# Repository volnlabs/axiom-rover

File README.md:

# Axiom Rover

**Interactive 3D inspection:** [open the hosted viewer](https://axiom-rover.vercel.app/) or [inspect the PCB](https://axiom-rover.vercel.app/?mode=pcb) — rotate, zoom, inspect all sides, hide the shell, or separate parts. [Local viewing and deployment instructions](viewer/README.md).

After cloning, use [the Git LFS checkout instructions](docs/build.md) to download the full assembly STEP, Pi reference STEP and viewer mesh before opening or rebuilding them.

A reusable 2WD release-test robot: one fixed Shrike/RP2040 + ForgeFPGA actuator base, a removable compute tray, an independent motor-power stop, and a wheels-raised stand. This is an **independent hardware repository**, not part of the AxiomOS source tree.

**Revision B is a design-review prototype, not released for fabrication or powered motion.** The carrier now has a bottom Pi 5 socket, two top Shrike R0.4 sockets, an onboard DRV8833 motor driver, and HC-SR04, wheel-encoder and IMU connectors. Vendor CAD and nominal socket models establish design coordinates; physical fit and powered tests remain outstanding.

- [Editable KiCad project](electronics/carrier.kicad_pro), [schematic](electronics/carrier.kicad_sch), [routed PCB](electronics/carrier.kicad_pcb), and [schematic drawing](electronics/out/schematic/carrier.svg).
- [Parametric mechanical source](mechanical/axiom_rover.py), [STEP assembly](mechanical/out/axiom_rover_assembly.step), and individual STL parts in [mechanical/out](mechanical/out/).
- [Electrical and harness contract](docs/electrical-contract.md), [wiring diagram](docs/harness.svg), [mechanical interfaces](docs/mechanical.md), [system BOM](bom/system-bom.csv).
- [Assembly, procurement and commissioning](docs/commissioning.md), [post-v1.0 compute roadmap](docs/compute-roadmap.md), [reproduction instructions](docs/build.md).
- [Controller bench fixture and motor-disconnected test procedure](docs/bench.md).
- [Native electrical check results](electronics/out/drc.json), [mechanical checks](mechanical/out/mechanical_checks.json), [populated assembly checks](mechanical/out/assembly-fit.json), [42 browser checks](viewer/browser-check.json), and [release gates](release-gates.json).

The carrier is 160 × 100 × 1.6 mm, two layers, with a cooler aperture. The Pi sits below it at a 16.5 mm gap and Shrike plugs into two 19-position sockets above. Two 6 V ThinkRobotics MOT3001-6V60RPM encoder motors drive 80 mm Pololu 3690 wheels. DRV8833 current regulation targets 1 A per channel; actual current and thermal behavior require bench measurements. The external fuse, normally-open motor-power relay, regulated motor source and separate host/base supplies remain off-board. Power down before compute swaps; J1 and alternate-host J12 cannot be used together.

A robot supplies repeatable evidence for named releases and fault cases. It cannot prove AxiomOS correct under every possible condition. Every physical result must identify the software/FPGA hashes, hardware revision, power state and raw capture.

Budget cap: ₹30,000 excluding compute boards and instruments, with ₹6,000 reserved for a revision. The current estimate is ₹20,821.98–₹45,459.98 before reserve (₹26,821.98–₹51,459.98 including it), not a vendor quote. First-order quotes must total at most ₹24,000 before ordering. Nothing has been purchased, fabricated, flashed or physically tested here.

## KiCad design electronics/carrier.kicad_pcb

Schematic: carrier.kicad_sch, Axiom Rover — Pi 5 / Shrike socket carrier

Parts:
C1, C2, C3, C4, C9: 100nF 16V X7R; C_0805_2012Metric
C5: 10uF 16V X7R; C_1206_3216Metric
C6: 10nF 25V X7R; C_0805_2012Metric
C7: 2.2uF 16V X7R; C_0805_2012Metric
C8: 470uF 16V; CP_Radial_D8.0mm_P3.50mm
D1: SMBJ6.0A; D_SMB
J1: ESQ-120-24-G-D_PI5_BOTTOM; Pi5_Socket_2x20
J2: SHRIKE_J2_SSW-119-01-G-S; SSW-119-01-G-S
J3: HC_SR04_VCC_TRIG_ECHO_GND; JST_XH_B4B-XH-A_1x04_P2.50mm_Vertical
J4: SHRIKE_J4_SSW-119-01-G-S; SSW-119-01-G-S
J5: ESTOP_LOGIC_NC; JST_XH_B2B-XH-A_1x02_P2.50mm_Vertical
J6: BASE_SENSOR_5V_IN; JST_XH_B2B-XH-A_1x02_P2.50mm_Vertical
J7: 6V_AFTER_FUSE_AND_STOP_RELAY; JST_VH_B2P-VH_1x02_P3.96mm_Vertical
J8: LEFT_MOTOR; JST_VH_B2P-VH_1x02_P3.96mm_Vertical
J9: RIGHT_MOTOR; JST_VH_B2P-VH_1x02_P3.96mm_Vertical
J10: ENCODER_LEFT_3V3; JST_XH_B4B-XH-A_1x04_P2.50mm_Vertical
J11: ENCODER_RIGHT_3V3; JST_XH_B4B-XH-A_1x04_P2.50mm_Vertical
J12: ALTERNATE_HOST_UART; JST_XH_B4B-XH-A_1x04_P2.50mm_Vertical
J13: IMU_3V3_I2C_INT; JST_XH_B5B-XH-A_1x05_P2.50mm_Vertical
R1, R16, R17, R18, R19: 1k 1%; R_0805_2012Metric
R2: 2.2k 1%; R_0805_2012Metric
R3: 3.3k 1%; R_0805_2012Metric
R4, R5, R6, R9, R10, R11, R12, R13: 10k 1%; R_0805_2012Metric
R7, R8: 0.20R 1W CSRT1206FTR200; R_1206_3216Metric
R14, R15: 4.7k 1%; R_0805_2012Metric
TP1: HOST_3V3; TestPoint_Pad_D1.5mm
TP2: H_GND; TestPoint_Pad_D1.5mm
TP3: BASE_3V3; TestPoint_Pad_D1.5mm
TP4: BASE_5V; TestPoint_Pad_D1.5mm
TP5: MOTOR_6V; TestPoint_Pad_D1.5mm
TP6: BASE_GND; TestPoint_Pad_D1.5mm
TP7: ESTOP_N; TestPoint_Pad_D1.5mm
TP8: DRV_FAULT_N; TestPoint_Pad_D1.5mm
TP9: SENSE_L; TestPoint_Pad_D1.5mm
TP10: SENSE_R; TestPoint_Pad_D1.5mm
U1: ISO7721DR; SOIC-8_3.9x4.9mm_P1.27mm
U2: SN74LVC1G17DBVR; SOT-23-5
U3: DRV8833PWPR; HTSSOP-16-1EP_4.4x5mm_P0.65mm_EP3.4x5mm_Mask2.46x2.31mm_The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
U4: SN74LVC08ADR; SOIC-14_3.9x8.7mm_P1.27mm
U5: SN74LVC125ADR; SOIC-14_3.9x8.7mm_P1.27mm

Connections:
/BASE_3V3: C2.1, C3.1, C4.1, C9.1, J2.2, J4.2, J5.1, J10.2, J11.2, J13.2, R9.2, R14.2, R15.2, TP3.1, U1.8 (VCC2), U2.5 (VCC), U4.14 (VCC), U5.14 (VCC)
/BASE_5V: J3.1, J6.1, TP4.1
/BASE_GND: C2.2, C3.2, C4.2, C5.2, C7.2, C8.2, C9.2, D1.2 (A), J2.8, J2.13, J3.4, J4.7, J4.13, J4.19, J6.2, J7.2, J10.1, J11.1, J13.1, R3.2, R4.2, R5.2, R6.2, R7.2, R8.2, R10.2, R11.2, R12.2, R13.2, TP6.1, U1.5 (GND2), U2.3 (GND), U3.13 (GND), U3.17 (EP), U4.7 (GND), U5.1 (1OE_N), U5.4 (2OE_N), U5.7 (GND), U5.10 (3OE_N), U5.13 (4OE_N)
/DRV_AIN1: U3.16 (AIN1), U4.3 (1Y)
/DRV_AIN2: U3.15 (AIN2), U4.6 (2Y)
/DRV_BIN1: U3.9 (BIN1), U4.8 (3Y)
/DRV_BIN2: U3.10 (BIN2), U4.11 (4Y)
/DRV_FAULT_N: R9.1, TP8.1, U3.8 (nFAULT), U5.9 (3A), U5.12 (4A)
/DRV_VCP: C6.1, U3.11 (VCP)
/DRV_VINT: C7.1, U3.14 (VINT)
/ECHO_DIV: R2.2, R3.1, U2.2 (A)
/ENC_L_A: J4.14, J10.3
/ENC_L_B: J4.12, J10.4
/ENC_R_A: J4.11, J11.3
/ENC_R_B: J4.10, J11.4
/ESTOP_FPGA: J2.16, R17.2
/ESTOP_FPGA_DRIVE: R17.1, U5.6 (2Y)
/ESTOP_N: J5.2, R4.1, TP7.1, U3.1 (nSLEEP), U5.2 (1A), U5.5 (2A)
/ESTOP_RP: J2.3, R16.2
/ESTOP_RP_DRIVE: R16.1, U5.3 (1Y)
/FAULT_FPGA_DRIVE: R19.1, U5.11 (4Y)
/FAULT_FPGA_N: J2.19, R19.2
/FAULT_RP_DRIVE: R18.1, U5.8 (3Y)
/FAULT_RP_N: J4.4, R18.2
/FPGA_PWM_L: J2.17, R5.1, U4.2 (1B), U4.5 (2B)
/FPGA_PWM_R: J2.18, R6.1, U4.10 (3B), U4.13 (4B)
/HOST_3V3: C1.1, J1.1, J1.17, J12.1, TP1.1, U1.1 (VCC1)
/H_GND: C1.2, J1.6, J1.9, J1.14, J1.20, J1.25, J1.30, J1.34, J1.39, J12.2, TP2.1, U1.4 (GND1)
/H_RX: J1.10, J12.4, U1.2 (OUTA)
/H_TX: J1.8, J12.3, U1.3 (INB)
/IMU_INT: J4.3, J13.5
/IMU_SCL: J4.5, J13.4, R15.1
/IMU_SDA: J4.6, J13.3, R14.1
/L_IN1: J2.4, R10.1, U4.1 (1A)
/L_IN2: J2.5, R11.1, U4.4 (2A)
/MOTOR_6V: C5.1, C6.2, C8.1, D1.1 (K), J7.1, TP5.1, U3.12 (VM)
/MOTOR_L_N: J8.2, U3.4 (AOUT2)
/MOTOR_L_P: J8.1, U3.2 (AOUT1)
/MOTOR_R_N: J9.2, U3.5 (BOUT2)
/MOTOR_R_P: J9.1, U3.7 (BOUT1)
/RP_UART_RX: J4.17, U1.6 (OUTB)
/RP_UART_TX: J4.18, U1.7 (INA)
/R_IN3: J2.6, R12.1, U4.9 (3A)
/R_IN4: J2.7, R13.1, U4.12 (4A)
/SENSE_L: R7.1, TP9.1, U3.3 (AISEN)
/SENSE_R: R8.1, TP10.1, U3.6 (BISEN)
/SENSOR_TRIG: J3.2, R1.2
/US_ECHO_3V: J2.10, U2.4 (Y)
/US_ECHO_5V: J3.3, R2.1
/US_TRIG: J2.9, R1.1

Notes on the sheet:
REV B.1: Pi 5 bottom socket + Shrike R0.4 top sockets; no host/base ground tie
J7: REGULATED 6 V AFTER EXTERNAL FUSE + INDEPENDENT STOP RELAY. 1 A nominal per motor.
FPGA PWM gates direction inputs through U4. nSLEEP is STOP level, never PWM.
Shrike USB-C is sole 5 V power entry. J1 pins 2/4 and J2/J4 pin 1 stay disconnected.
REVIEW ONLY: physical fit, current limit, cooling and firmware timing require bench evidence.

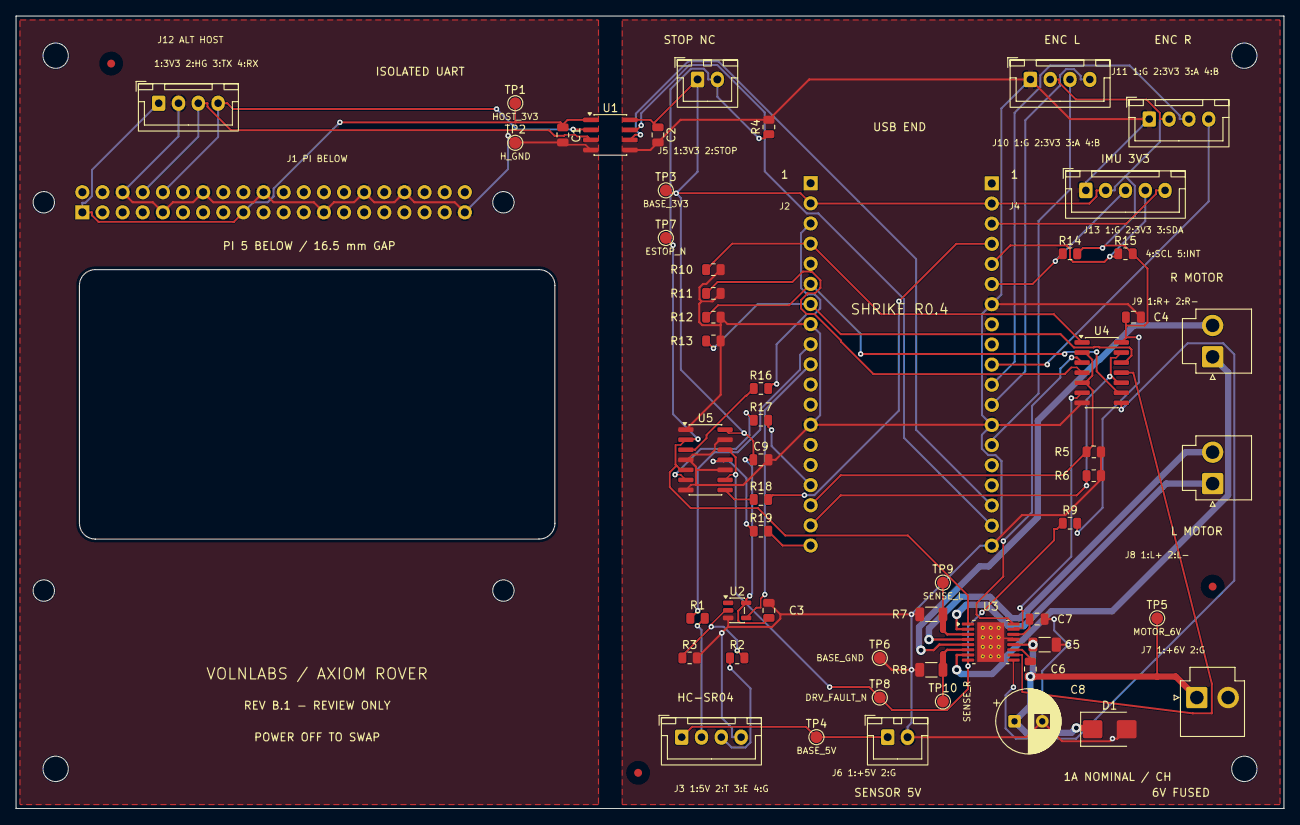
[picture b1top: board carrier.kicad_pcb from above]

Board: 2 copper layers, 160.0 x 100.0 mm, 68 parts (1 on the bottom side), 50 nets.

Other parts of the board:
FID1, FID2, FID3: Fiducial; Fiducial_1mm_Mask3mm
H1, H2, H3, H4: M3 NPTH; MountingHole_3.2mm_M3
H5, H6, H7, H8: M2.5 NPTH; MountingHole_2.7mm_M2.5

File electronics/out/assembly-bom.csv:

Reference,Value / MPN,Footprint,Quantity
J1,ESQ-120-24-G-D_PI5_BOTTOM,Rover:Pi5_Socket_2x20,1
J2,SHRIKE_J2_SSW-119-01-G-S,Rover:SSW-119-01-G-S,1
J4,SHRIKE_J4_SSW-119-01-G-S,Rover:SSW-119-01-G-S,1
U3,DRV8833PWPR,Package_SO:HTSSOP-16-1EP_4.4x5mm_P0.65mm_EP3.4x5mm_Mask2.46x2.31mm_ThermalVias,1
U4,SN74LVC08ADR,Package_SO:SOIC-14_3.9x8.7mm_P1.27mm,1
U1,ISO7721DR,Package_SO:SOIC-8_3.9x4.9mm_P1.27mm,1
C1,100nF 16V X7R,Capacitor_SMD:C_0805_2012Metric,1
C2,100nF 16V X7R,Capacitor_SMD:C_0805_2012Metric,1
J3,HC_SR04_VCC_TRIG_ECHO_GND,Connector_JST:JST_XH_B4B-XH-A_1x04_P2.50mm_Vertical,1
R1,1k 1%,Resistor_SMD:R_0805_2012Metric,1
R2,2.2k 1%,Resistor_SMD:R_0805_2012Metric,1
R3,3.3k 1%,Resistor_SMD:R_0805_2012Metric,1
U2,SN74LVC1G17DBVR,Package_TO_SOT_SMD:SOT-23-5,1
C3,100nF 16V X7R,Capacitor_SMD:C_0805_2012Metric,1
R4,10k 1%,Resistor_SMD:R_0805_2012Metric,1
R5,10k 1%,Resistor_SMD:R_0805_2012Metric,1
R6,10k 1%,Resistor_SMD:R_0805_2012Metric,1
R7,0.20R 1W CSRT1206FTR200,Resistor_SMD:R_1206_3216Metric,1
R8,0.20R 1W CSRT1206FTR200,Resistor_SMD:R_1206_3216Metric,1
R9,10k 1%,Resistor_SMD:R_0805_2012Metric,1
R10,10k 1%,Resistor_SMD:R_0805_2012Metric,1
R11,10k 1%,Resistor_SMD:R_0805_2012Metric,1
R12,10k 1%,Resistor_SMD:R_0805_2012Metric,1
R13,10k 1%,Resistor_SMD:R_0805_2012Metric,1
C4,100nF 16V X7R,Capacitor_SMD:C_0805_2012Metric,1
C5,10uF 16V X7R,Capacitor_SMD:C_1206_3216Metric,1
C6,10nF 25V X7R,Capacitor_SMD:C_0805_2012Metric,1
C7,2.2uF 16V X7R,Capacitor_SMD:C_0805_2012Metric,1
C8,470uF 16V,Capacitor_THT:CP_Radial_D8.0mm_P3.50mm,1
D1,SMBJ6.0A,Diode_SMD:D_SMB,1
J5,ESTOP_LOGIC_NC,Connector_JST:JST_XH_B2B-XH-A_1x02_P2.50mm_Vertical,1
J6,BASE_SENSOR_5V_IN,Connector_JST:JST_XH_B2B-XH-A_1x02_P2.50mm_Vertical,1
J7,6V_AFTER_FUSE_AND_STOP_RELAY,Connector_JST:JST_VH_B2P-VH_1x02_P3.96mm_Vertical,1
J8,LEFT_MOTOR,Connector_JST:JST_VH_B2P-VH_1x02_P3.96mm_Vertical,1
J9,RIGHT_MOTOR,Connector_JST:JST_VH_B2P-VH_1x02_P3.96mm_Vertical,1
J10,ENCODER_LEFT_3V3,Connector_JST:JST_XH_B4B-XH-A_1x04_P2.50mm_Vertical,1
J11,ENCODER_RIGHT_3V3,Connector_JST:JST_XH_B4B-XH-A_1x04_P2.50mm_Vertical,1
J12,ALTERNATE_HOST_UART,Connector_JST:JST_XH_B4B-XH-A_1x04_P2.50mm_Vertical,1
J13,IMU_3V3_I2C_INT,Connector_JST:JST_XH_B5B-XH-A_1x05_P2.50mm_Vertical,1
R14,4.7k 1%,Resistor_SMD:R_0805_2012Metric,1
R15,4.7k 1%,Resistor_SMD:R_0805_2012Metric,1
U5,SN74LVC125ADR,Package_SO:SOIC-14_3.9x8.7mm_P1.27mm,1
C9,100nF 16V X7R,Capacitor_SMD:C_0805_2012Metric,1
R16,1k 1%,Resistor_SMD:R_0805_2012Metric,1
R17,1k 1%,Resistor_SMD:R_0805_2012Metric,1
R18,1k 1%,Resistor_SMD:R_0805_2012Metric,1
R19,1k 1%,Resistor_SMD:R_0805_2012Metric,1

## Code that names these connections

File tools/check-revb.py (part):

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assert pins['J1']['2'] is None and pins['J1']['4'] is None, 'Pi 5 V must remain disconnected'
assert len(pins['J2']) == len(pins['J4']) == 19, 'Missing physical Shrike rows'
assert pins['J2']['1'] is pins['J4']['1'] is None, 'Shrike USB is the sole 5 V power entry'
assert pins['J4']['14'] == 'ENC_L_A' and pins['J4']['12'] == 'ENC_L_B'
assert pins['J4']['11'] == 'ENC_R_A' and pins['J4']['10'] == 'ENC_R_B'
assert pins['J4']['6'] == 'IMU_SDA' and pins['J4']['5'] == 'IMU_SCL'
assert pins['J4']['4']=='FAULT_RP_N' and pins['J2']['19']=='FAULT_FPGA_N'
assert pins['J2']['3']=='ESTOP_RP' and pins['J2']['16']=='ESTOP_FPGA'
assert pins['U3']['8']=='DRV_FAULT_N' and pins['U3']['1']=='ESTOP_N'
assert not {'ESTOP_N','DRV_FAULT_N'} & set(pins['J2'].values())
assert not {'ESTOP_N','DRV_FAULT_N'} & set(pins['J4'].values())
buffer=['BASE_GND','ESTOP_N','ESTOP_RP_DRIVE','BASE_GND','ESTOP_N','ESTOP_FPGA_DRIVE','BASE_GND','FAULT_RP_DRIVE','DRV_FAULT_N','BASE_GND','FAULT_FPGA_DRIVE','DRV_FAULT_N','BASE_GND','BASE_3V3']
assert pins['U5']=={str(i):n for i,n in enumerate(buffer,1)}
for ref,source,destination in [('R16','ESTOP_RP_DRIVE','ESTOP_RP'),('R17','ESTOP_FPGA_DRIVE','ESTOP_FPGA'),('R18','FAULT_RP_DRIVE','FAULT_RP_N'),('R19','FAULT_FPGA_DRIVE','FAULT_FPGA_N')]:
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            'DRV_VCP','MOTOR_6V','BASE_GND','DRV_VINT','DRV_AIN2','DRV_AIN1','BASE_GND']
assert pins['U3'] == {str(i): n for i,n in enumerate(expected,1)}, 'Driver PWP pinout'
for ref in ('R7','R8'):
    assert pins[ref]['2'] == 'BASE_GND', 'Sense resistor return'
assert pins['J3'] == {'1':'BASE_5V','2':'SENSOR_TRIG','3':'US_ECHO_5V','4':'BASE_GND'}
# Check the actual quad-AND wiring against the TI pin grouping, then its coast state.
for a,b,y,signal,pwm,output in [(1,2,3,'L_IN1','FPGA_PWM_L','DRV_AIN1'),(4,5,6,'L_IN2','FPGA_PWM_L','DRV_AIN2'),(9,10,8,'R_IN3','FPGA_PWM_R','DRV_BIN1'),(12,13,11,'R_IN4','FPGA_PWM_R','DRV_BIN2')]:
    assert [pins['U4'][str(p)] for p in (a,b,y)] == [signal,pwm,output]
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        assert any({tuple(e['start']),tuple(e['end'])}=={a,z} and math.dist(e['mid'],mid)<1e-5 for a,z,mid in arc_geometry), 'Cooler corner radius changed'
assert len(fp['U3']['thermal_vias'])==12 and all(p['net']=='BASE_GND' and p['drill']==.2 for p in fp['U3']['thermal_vias'])
for ref in ('J1','J2','J3','J4','J6','J10','J11','J12','J13'):
    assert all(p['thermal_relief'] for p in fp[ref]['pins'].values() if p['net'] in ('H_GND','BASE_GND')), ('Hand solder relief',ref)
assert not fp['J7']['pins']['2']['thermal_relief'], 'Motor return must retain direct copper'
for i,net in enumerate(['HOST_3V3','H_GND','BASE_3V3','BASE_5V','MOTOR_6V','BASE_GND','ESTOP_N','DRV_FAULT_N','SENSE_L','SENSE_R'],1):
    ref=f'TP{i}'; p=fp[ref]
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            if score<best.get(nxt,math.inf): best[nxt]=score; heapq.heappush(queue,(score,nxt))
    raise AssertionError(('No continuous local F.Cu path',net,start,end))

for net,pin,ref,limit in [('SENSE_L','3','R7',7),('SENSE_R','6','R8',7),('MOTOR_6V','12','C5',4),('DRV_VINT','14','C7',4),('DRV_VCP','11','C6',3)]:
    def pos(ref,pin): return tuple(round(fp[ref]['pins'][pin][a],4) for a in ('x','y'))
    length=route_length(net,pos('U3',pin),pos(ref,'1'))
    assert length<=limit+.001, (net,length,limit)
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
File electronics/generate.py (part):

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# ref, value, footprint, physical-pad-ordered nets, PCB x/y/angle, schematic x/y
# J1 is fitted BELOW the PCB; its pad numbers are stated in top-board coordinates.
PI_NETS=[None]*40
for pin,net in {1:'HOST_3V3',17:'HOST_3V3',6:'H_GND',9:'H_GND',14:'H_GND',20:'H_GND',25:'H_GND',30:'H_GND',34:'H_GND',39:'H_GND',8:'H_TX',10:'H_RX'}.items(): PI_NETS[pin-1]=net
SENSOR_FP=lambda n: xh(n)
POWER_FP='Connector_JST:JST_VH_B2P-VH_1x02_P3.96mm_Vertical'
DRV_FP='Package_SO:HTSSOP-16-1EP_4.4x5mm_P0.65mm_EP3.4x5mm_Mask2.46x2.31mm_ThermalVias'
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
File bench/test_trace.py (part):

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    def test_rejects_wiring_mismatch_outside_tolerance(self):
        rows = self.valid_rows()
        rows[3]["time_us"] = 17
        rows[3]["drv_ain1"] = 0
        self.assertFalse(self.evaluate(rows)["passed"])

    def test_rejects_late_stop(self):
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    def test_software_stop_may_hold_nsleep_high(self):
        rows = self.valid_rows()
        for row in rows:
            row["estop_n"] = row["nsleep"] = 1
        self.assertTrue(self.evaluate(rows)["passed"])

    def test_rejects_sample_gaps_above_declared_limit(self):
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
    def test_rejects_non_low_startup(self):
        rows = self.valid_rows()
        rows[0]["l_in1"] = 1
        self.assertFalse(self.evaluate(rows)["passed"])

    def test_rejects_invalid_or_posthoc_manifest(self):
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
